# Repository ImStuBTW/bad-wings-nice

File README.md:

# Bad Wings "Nice!"

A variant of [Hazel](https://github.com/hazels-garage/)'s popular [Bad Wings](https://github.com/hazels-garage/bad-wings/tree/master/v2) keyboard adapted to use the Nice!Nano microcontroller. Hazel mentioned this should exist recently, and now it does. This was a fun weekend lark that I have no intention of ever personally fabricating. Consider this an unofficial dabbling in the [Democratic Ergonomic Keyboard](https://github.com/the-democratic-ergo-keyboard/manifesto) initiative.

It uses a standard Nice!Nano stack. The microcontroller should be mounted face-down on a socket. There should be enough room underneath the microcontroller to house a LiPo battery. You can attach it via a JST header, or just solder it directly onto a board. A small slide switch breaks the connection to the battery's ground to turn the microcontroller on and off.

A footprint has been added for a Nice!View display. There were *just* enough pins to give the Nice!View and the Cirque trackpad header their own dedicated CS pins. I haven't tested them in tandem together. I also haven't written a ZMK firmware for this keyboard. Again, I've never actually built this.

There's a chance the bottom piece of the existing 3D printed case would fit this keyboard. The PCB outline hasn't changed. The power switch should overlap with the existing USB port cutout. The Cirque trackpad header was moved down several millimeters to make room for the Nice!View header. The switch plate and top piece may need adjustments to account for the Nice!Nano stack's height. As originally designed, the Nice!View display and trackpad will overlap.

The key switches are Choc spaced. The stems are Choc v2 compatible however. I believe there's some 3D printed keycaps that support Choc v2 switches but are Choc v1 spaced, so this board should be usable with either switch.

## Features

- 36 key unibody split
- Choc v1 spaced, Choc v1 and v2 supported, column staggered layout
- Gentle splay on ring and pinky columns
- Nice!Nano compatible
- Nice!View support
- Cirque touchpad support
- Built in mounting standoffs
- 3D Printed Case?

## Special Thanks

[Hazel](https://github.com/hazels-garage/) for designing the original [Bad Wings](https://github.com/hazels-garage/bad-wings/tree/master/v2) keyboard, and Fingerpunch's regular cast of Discord characters encouraging me to actually finish routing this.

Let me know if you actually make this. Good luck.

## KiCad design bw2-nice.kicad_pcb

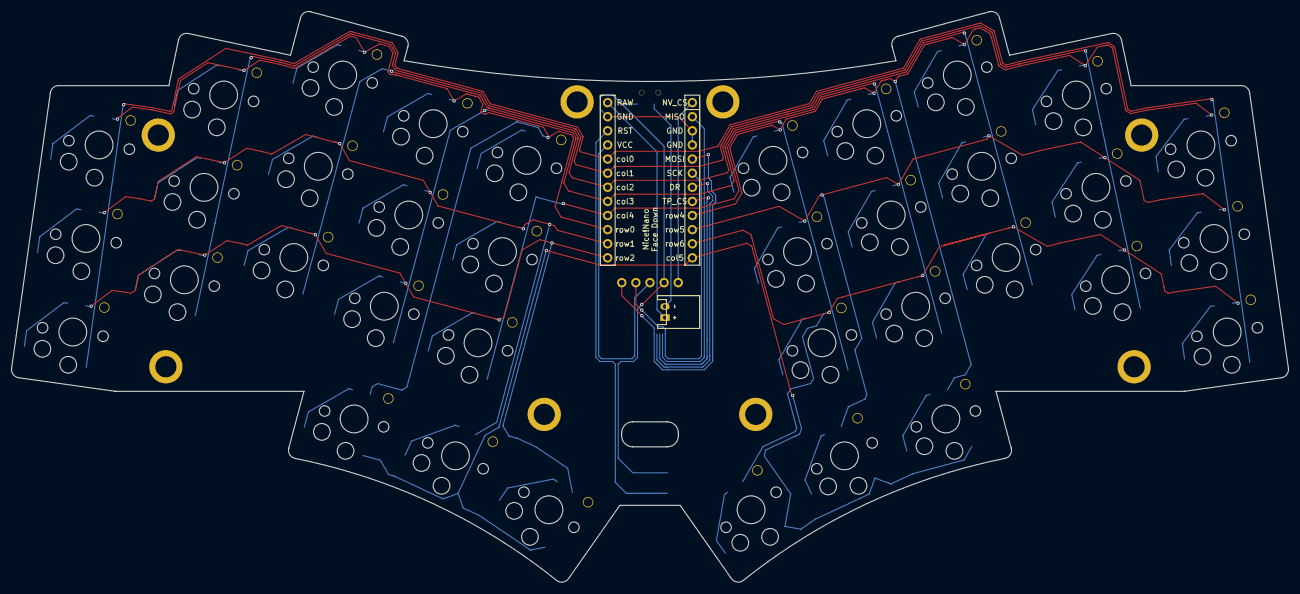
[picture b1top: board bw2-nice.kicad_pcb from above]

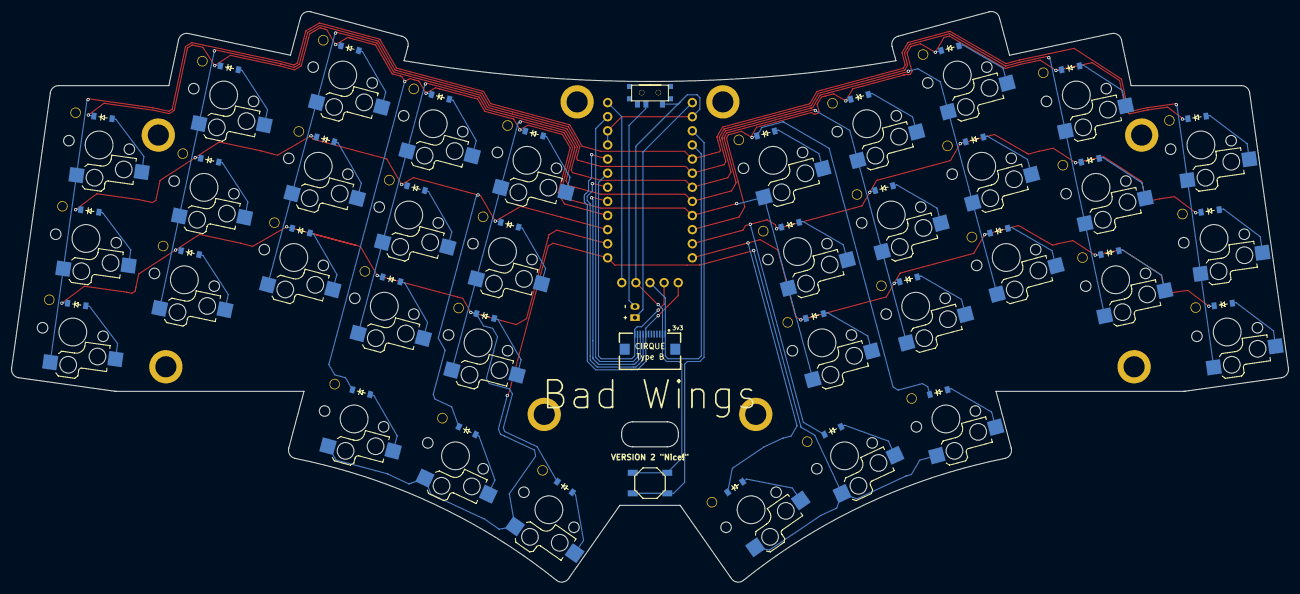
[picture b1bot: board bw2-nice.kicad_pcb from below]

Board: 2 copper layers, 229.8 x 102.7 mm, 86 parts (73 on the bottom side), 59 nets.

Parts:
B1: SW_TACT_ALPS_SKQGABE010
D1, D2, D3, D4, D5, D6, D7, D8, D9, D10, D11, D12, D13, D14, D15, D16, D17, D18, D19, D20, D21, D22, D23, D24, D25, D26, D27, D28, D29, D30, D31, D32, D33, D34, D35, D36: diode_tht_sod123
DISP1: display_nice_view
H1, H2, H3, H4, H5, H6, H7, H8: mounting_hole_plated
JST1: JST_PH_S2B-PH-K_02x2.00mm_Angled
MCU1: mcu_nice_nano
S1, S2, S3, S4, S5, S6, S7, S8, S9, S10, S11, S12, S13, S14, S15, S16, S17, S18, S19, S20, S21, S22, S23, S24, S25, S26, S27, S28, S29, S30, S31, S32, S33, S34, S35, S36: switch_choc_v1_v2
T1: SPDT_C128955
XX1: vik-keyboard-connector-horizontal

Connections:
BAT-: JST1.2, T1.2
DR: MCU1.7, XX1.9
GND: B1.1, DISP1.4, MCU1.3, MCU1.4, MCU1.23, T1.1, XX1.2
MISO: MCU1.2, XX1.11
MOSI: DISP1.1, MCU1.5, XX1.8
NV_CS: DISP1.5, MCU1.1
RAW: JST1.1, MCU1.24
RST: B1.2, MCU1.22
SCK: DISP1.2, MCU1.6, XX1.12
TP_CS: MCU1.8, XX1.10
VCC: DISP1.3, MCU1.21, XX1.1
c0_bottom: D1.2, S1.2
c0_home: D2.2, S2.2
c0_top: D3.2, S3.2
c1_bottom: D4.2, S4.2
c1_home: D5.2, S5.2
c1_top: D6.2, S6.2
c2_bottom: D7.2, S7.2
c2_home: D8.2, S8.2
c2_thumbs: D31.2, S31.2
c2_top: D9.2, S9.2
c3_bottom: D10.2, S10.2
c3_home: D11.2, S11.2
c3_thumbs: D32.2, S32.2
c3_top: D12.2, S12.2
c4_bottom: D13.2, S13.2
c4_home: D14.2, S14.2
c4_thumbs: D33.2, S33.2
c4_top: D15.2, S15.2
col0: MCU1.20, S1.1, S2.1, S3.1, S16.1, S17.1, S18.1
col1: MCU1.19, S4.1, S5.1, S6.1, S19.1, S20.1, S21.1
col2: MCU1.18, S7.1, S8.1, S9.1, S22.1, S23.1, S24.1
col3: MCU1.17, S10.1, S11.1, S12.1, S25.1, S26.1, S27.1
col4: MCU1.16, S13.1, S14.1, S15.1, S28.1, S29.1, S30.1
col5: MCU1.12, S31.1, S32.1, S33.1, S34.1, S35.1, S36.1
mirror_c0_bottom: D16.2, S16.2
mirror_c0_home: D17.2, S17.2
mirror_c0_top: D18.2, S18.2
mirror_c1_bottom: D19.2, S19.2
mirror_c1_home: D20.2, S20.2
mirror_c1_top: D21.2, S21.2
mirror_c2_bottom: D22.2, S22.2
mirror_c2_home: D23.2, S23.2
mirror_c2_thumbs: D34.2, S34.2
mirror_c2_top: D24.2, S24.2
mirror_c3_bottom: D25.2, S25.2
mirror_c3_home: D26.2, S26.2
mirror_c3_thumbs: D35.2, S35.2
mirror_c3_top: D27.2, S27.2
mirror_c4_bottom: D28.2, S28.2
mirror_c4_home: D29.2, S29.2
mirror_c4_thumbs: D36.2, S36.2
mirror_c4_top: D30.2, S30.2
row0: D3.1, D6.1, D9.1, D12.1, D15.1, D31.1, MCU1.15
row1: D2.1, D5.1, D8.1, D11.1, D14.1, D32.1, MCU1.14
row2: D1.1, D4.1, D7.1, D10.1, D13.1, D33.1, MCU1.13
row4: D18.1, D21.1, D24.1, D27.1, D30.1, D34.1, MCU1.9
row5: D17.1, D20.1, D23.1, D26.1, D29.1, D35.1, MCU1.10
row6: D16.1, D19.1, D22.1, D25.1, D28.1, D36.1, MCU1.11

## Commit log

2025-12-09 Init Commit
2025-12-09 Added license.
